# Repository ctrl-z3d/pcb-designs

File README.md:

# pcb-designs

A personal archive of PCB projects I've designed and built along the way. Schematics, board layouts, manufacturing files, and notes. This repo is mostly a learning log and reference for myself, but feel free to poke around if you found it useful.

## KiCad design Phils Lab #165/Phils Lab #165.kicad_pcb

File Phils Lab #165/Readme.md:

# Phil's Lab #165

KiCad project files for Phil's Lab video #165.

## Schematic

## PCB Layout

## 3D View (Top)

## 3D View (Bottom)

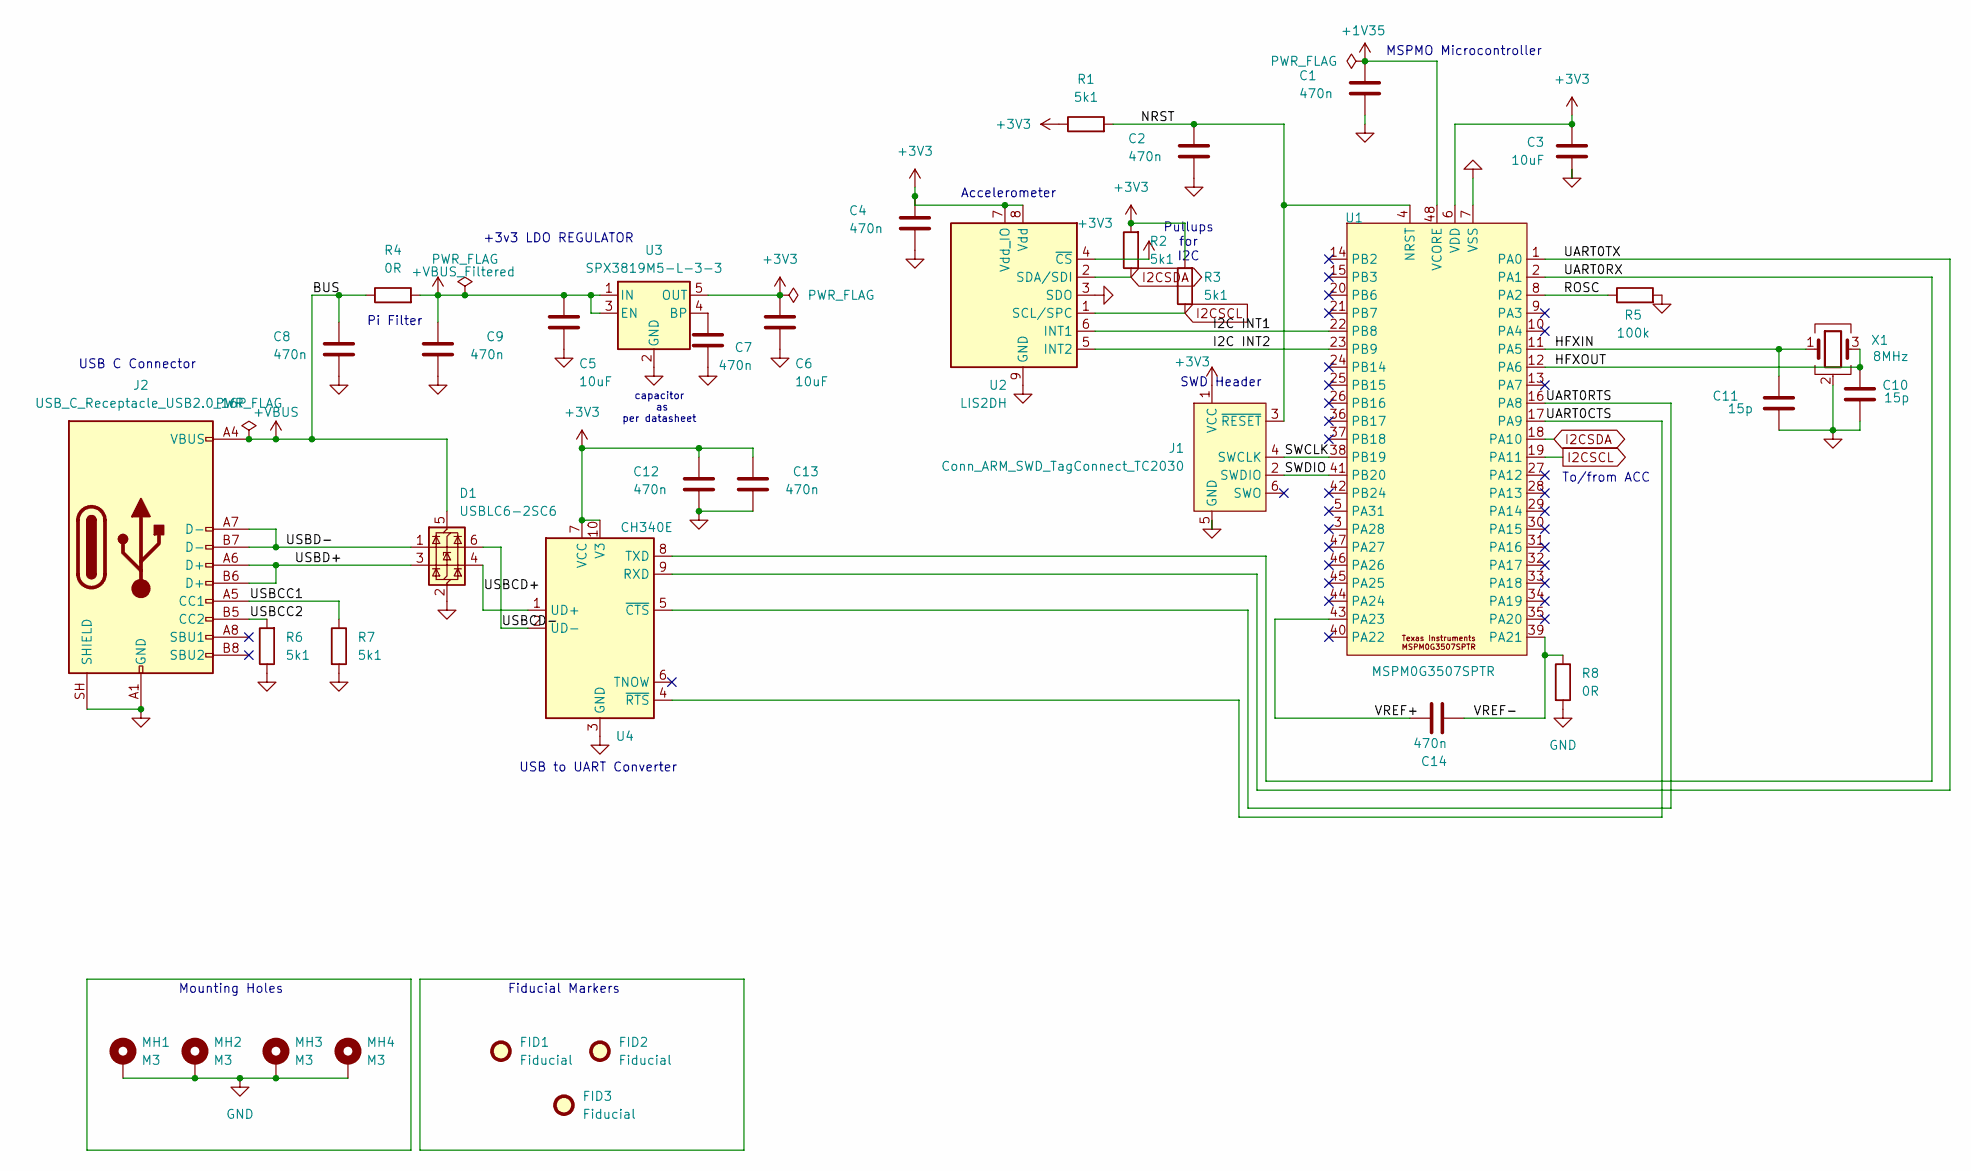
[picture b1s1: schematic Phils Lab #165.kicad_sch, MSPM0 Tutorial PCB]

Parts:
C1, C2, C4, C7, C8, C9, C12, C13, C14: 470n; C_0603_1608Metric
C3, C5, C6: 10uF; C_0805_2012Metric
C10, C11: 15p; C_0603_1608Metric
D1: USBLC6-2SC6; SOT-23-6
FID1, FID2, FID3: Fiducial; Fiducial_1mm_Mask2mm
J1: Conn_ARM_SWD_TagConnect_TC2030; Tag-Connect_TC2030-IDC-FP_2x03_P1.27mm_Vertical
J2: USB_C_Receptacle_USB2.0_16P; USB_C_Receptacle_GCT_USB4105-xx-A_16P_TopMnt_Horizontal
MH1, MH2, MH3, MH4: M3; MountingHole_3.2mm_M3_Pad_Via
R1, R2, R3, R6, R7: 5k1; R_0603_1608Metric_Pad0.98x0.95mm_HandSolder
R4, R8: 0R; R_0603_1608Metric_Pad0.98x0.95mm_HandSolder
R5: 100k; R_0603_1608Metric_Pad0.98x0.95mm_HandSolder
U1: MSPM0G3507SPTR; PT0048A-IPC_A
U2: LIS2DH; LGA-14_2x2mm_P0.35mm_LayoutBorder3x4y
U3: SPX3819M5-L-3-3; SOT-23-5
U4: CH340E; MSOP-10_3x3mm_P0.5mm
X1: 8MHz; Crystal_SMD_3225-4Pin_3.2x2.5mm

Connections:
+1V35: C1.1, U1.48 (VCORE)
+3V3: C3.1, C4.1, C6.1, C12.1, C13.1, J1.1 (VCC), R1.1, R2.2, R3.2, U1.6 (VDD), U2.4 (~CS), U2.7 (Vdd_IO), U2.8 (Vdd), U3.5 (OUT), U4.7 (VCC), U4.10 (V3)
+VBUS: C8.1, D1.5 (VBUS), J2.A4 (VBUS), J2.A9 (VBUS), J2.B4 (VBUS), J2.B9 (VBUS), R4.1
+VBUS_Filtered: C5.1, C9.1, R4.2, U3.1 (IN), U3.3 (EN)
/HFXIN: C11.1, U1.11 (PA5), X1.1
/HFXOUT: C10.1, U1.12 (PA6), X1.3
/I2C INT1: U1.22 (PB8), U2.6 (INT1)
/I2C INT2: U1.23 (PB9), U2.5 (INT2)
/NRST: C2.1, J1.3 (~RESET), R1.2, U1.4 (NRST)
/ROSC: R5.1, U1.8 (PA2)
/SWCLK: J1.4 (SWCLK), U1.38 (PB19)
/SWDIO: J1.2 (SWDIO), U1.41 (PB20)
/UART0CTS: U1.17 (PA9), U4.4 (~RTS)
/UART0RTS: U1.16 (PA8), U4.5 (~CTS)
/UART0RX: U1.2 (PA1), U4.8 (TXD)
/UART0TX: U1.1 (PA0), U4.9 (RXD)
/USBCC1: J2.A5 (CC1), R7.1
/USBCC2: J2.B5 (CC2), R6.2
/USBCD+: D1.4 (I/O2), U4.1 (UD+)
/USBCD-: D1.6 (I/O1), U4.2 (UD-)
/USBD+: D1.3 (I/O2), J2.A6 (D+), J2.B6 (D+)
/USBD-: D1.1 (I/O1), J2.A7 (D-), J2.B7 (D-)
/VREF+: C14.1, U1.43 (PA23)
/VREF-: C14.2, R8.1, U1.39 (PA21)
GND: C1.2, C2.2, C3.2, C4.2, C5.2, C6.2, C7.2, C8.2, C9.2, C10.2, C11.2, C12.2, C13.2, D1.2 (GND), J1.5 (GND), J2.A1 (GND), J2.A12 (GND), J2.B1 (GND), J2.B12 (GND), J2.SH (SHIELD), MH1.1 (1_1), MH2.1 (1_1), MH3.1 (1_1), MH4.1 (1_1), R5.2, R6.1, R7.2, R8.2, U1.7 (VSS), U2.3 (SDO), U2.9 (GND), U2.10 (GND), U2.11 (GND), U2.12 (GND), U2.13 (GND), U2.14 (GND), U3.2 (GND), U4.3 (GND), X1.2 (G), X1.4 (G)
I2CSCL: R3.1, U1.19 (PA11), U2.1 (SCL/SPC)
I2CSDA: R2.1, U1.18 (PA10), U2.2 (SDA/SDI)
unnamed: C7.1, U3.4 (BP)

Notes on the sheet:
MSPMO Microcontroller
Accelerometer
Mounting Holes
To/from ACC
USB C Connector
Fiducial Markers
Pi Filter
USB to UART Converter
capacitor as per datasheet
Pullups for I2C
+3v3 LDO REGULATOR
SWD Header

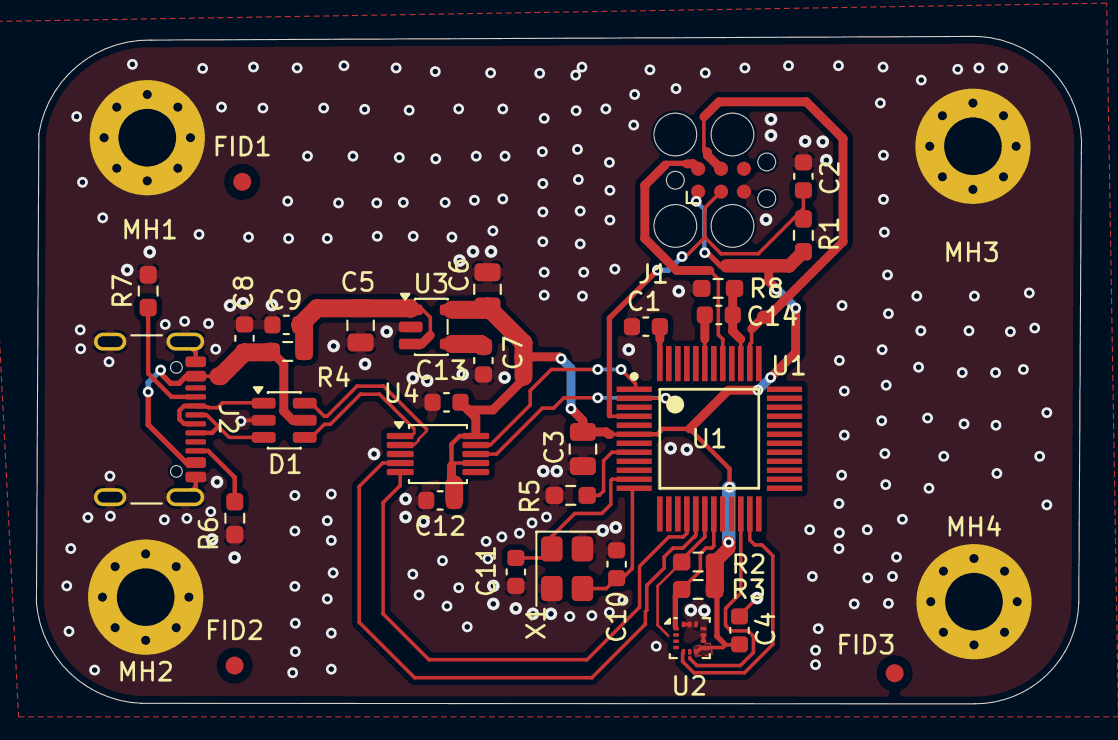
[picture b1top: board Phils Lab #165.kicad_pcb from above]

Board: 2 copper layers, 58.1 x 37.1 mm, 37 parts (0 on the bottom side), 28 nets.

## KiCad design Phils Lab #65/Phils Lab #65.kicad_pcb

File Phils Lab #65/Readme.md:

# Phil's Lab #65

KiCad project files for Phil's Lab video #65.

## Schematic

## PCB Layout

## 3D View

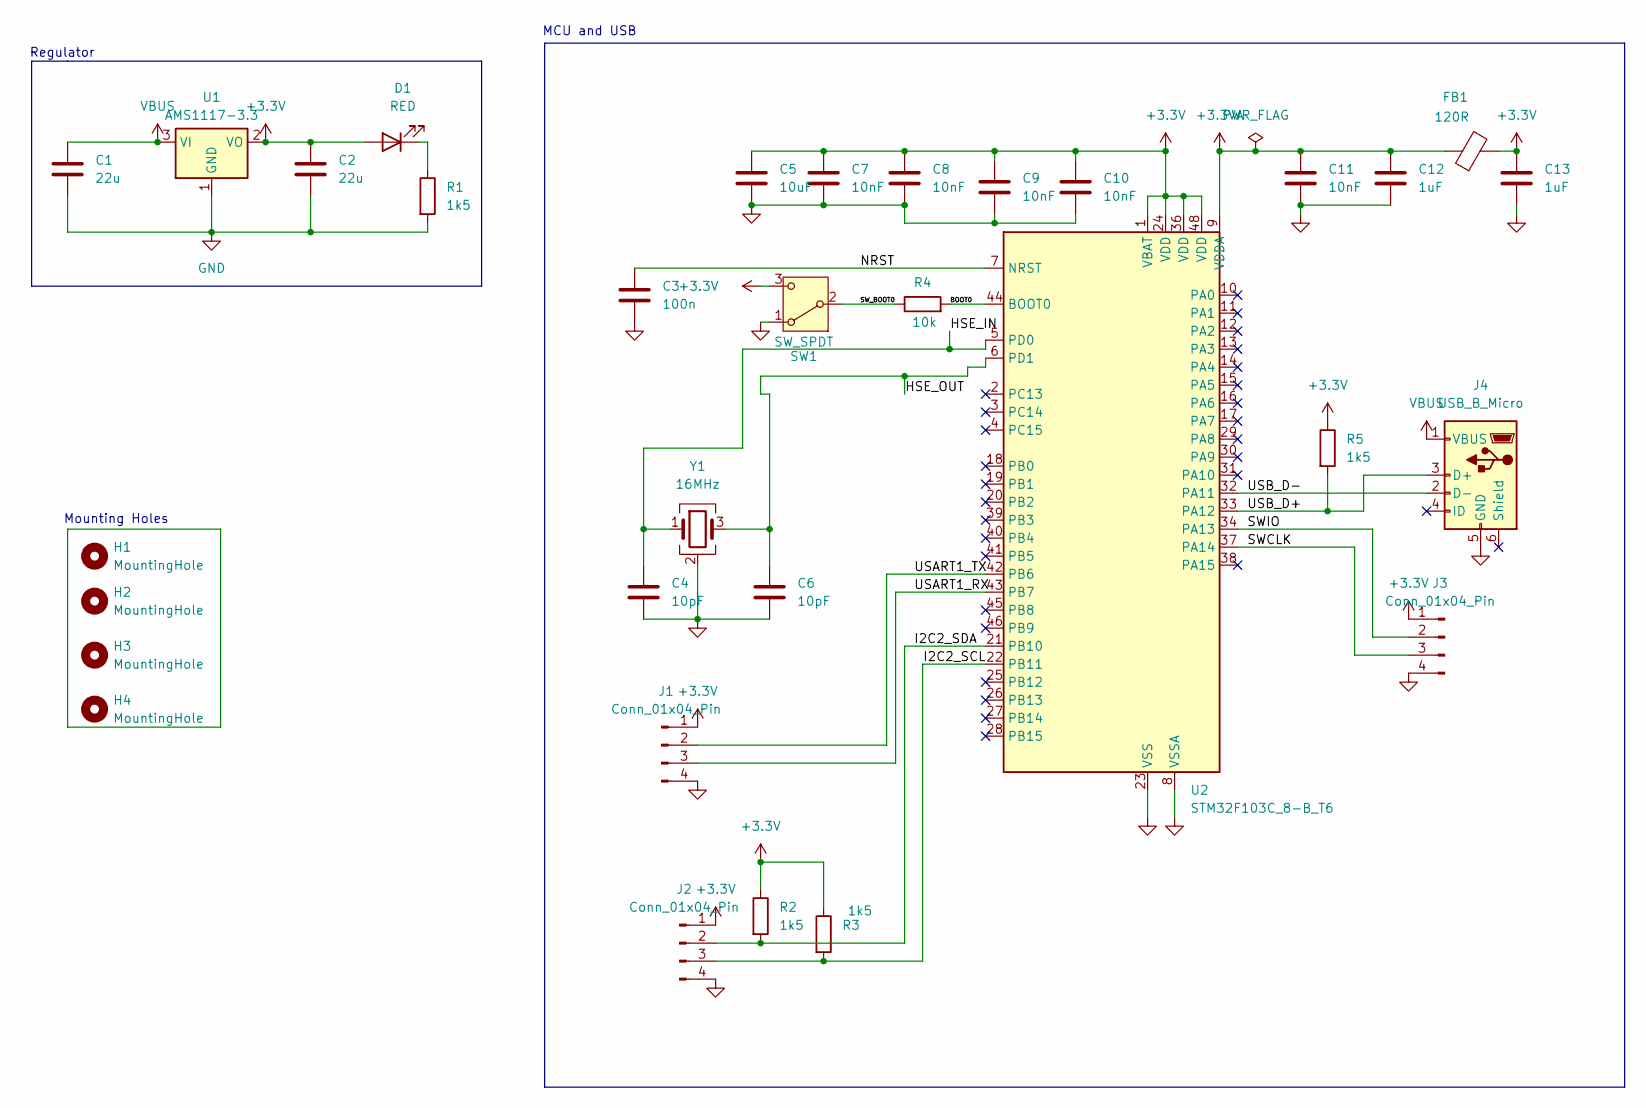
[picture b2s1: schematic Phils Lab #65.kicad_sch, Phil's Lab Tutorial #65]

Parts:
C1, C2: 22u; C_0805_2012Metric
C3: 100n; C_0402_1005Metric_Pad0.74x0.62mm_HandSolder
C4: 10pF; C_0402_1005Metric
C5: 10uF; C_0603_1608Metric_Pad1.08x0.95mm_HandSolder
C6: 10pF; C_0402_1005Metric_Pad0.74x0.62mm_HandSolder
C7, C8, C9, C10, C11: 10nF; C_0402_1005Metric
C12, C13: 1uF; C_0402_1005Metric
D1: RED; LED_0603_1608Metric
FB1: 120R; L_0603_1608Metric
H1, H2, H3, H4: MountingHole; MountingHole_2.2mm_M2
J1, J2, J3: Conn_01x04_Pin; Molex_KK-254_AE-6410-04A_1x04_P2.54mm_Vertical
J4: USB_B_Micro; USB_Micro-B_Wuerth_629105150521_CircularHoles
R1, R2, R3, R5: 1k5; R_0402_1005Metric_Pad0.72x0.64mm_HandSolder
R4: 10k; R_0402_1005Metric_Pad0.72x0.64mm_HandSolder
SW1: SW_SPDT; SW_SPDT_PCM12
U1: AMS1117-3.3; SOT-223-3_TabPin2
U2: STM32F103C_8-B_T6; LQFP-48_7x7mm_P0.5mm
Y1: 16MHz; Crystal_SMD_3225-4Pin_3.2x2.5mm

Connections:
+3.3V: C2.1, C5.1, C7.1, C8.1, C9.1, C10.1, C13.1, D1.2 (A), FB1.2, J1.1, J2.1, J3.1, R2.1, R3.1, R5.1, SW1.3 (C), U1.2 (VO), U2.1 (VBAT), U2.24 (VDD), U2.36 (VDD), U2.48 (VDD)
+3.3VA: C11.1, C12.1, FB1.1, U2.9 (VDDA)
/BOOT0: R4.2, U2.44 (BOOT0)
/HSE_IN: C4.1, U2.5 (PD0), Y1.1
/HSE_OUT: C6.1, U2.6 (PD1), Y1.3
/I2C2_SCL: J2.3, R3.2, U2.22 (PB11)
/I2C2_SDA: J2.2, R2.2, U2.21 (PB10)
/NRST: C3.1, U2.7 (NRST)
/SWCLK: J3.3, U2.37 (PA14)
/SWIO: J3.2, U2.34 (PA13)
/SW_BOOT0: R4.1, SW1.2 (B)
/USART1_RX: J1.3, U2.43 (PB7)
/USART1_TX: J1.2, U2.42 (PB6)
/USB_D+: J4.3 (D+), R5.2, U2.33 (PA12)
/USB_D-: J4.2 (D-), U2.32 (PA11)
GND: C1.2, C2.2, C3.2, C4.2, C5.2, C6.2, C7.2, C8.2, C9.2, C10.2, C11.2, C12.2, C13.2, J1.4, J2.4, J3.4, J4.5 (GND), R1.2, SW1.1 (A), U1.1 (GND), U2.8 (VSSA), U2.23 (VSS), Y1.2 (G), Y1.4 (G)
unnamed: D1.1 (K), R1.1
VBUS: C1.1, J4.1 (VBUS), U1.3 (VI)

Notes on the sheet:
MCU and USB
Regulator
Mounting Holes

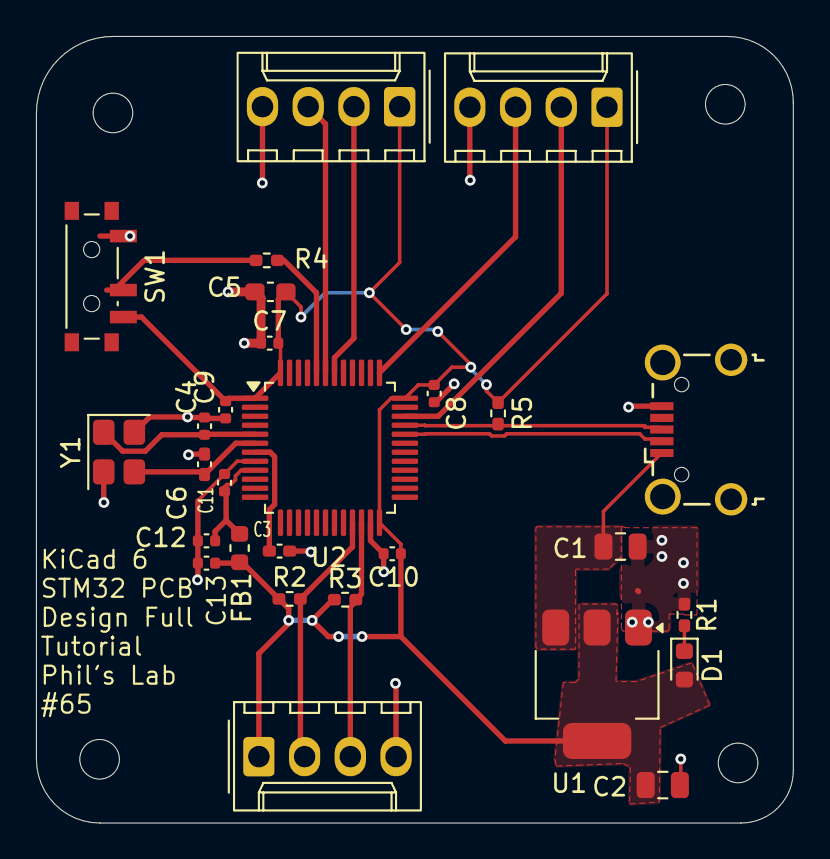
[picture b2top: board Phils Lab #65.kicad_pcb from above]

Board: 2 copper layers, 42.0 x 43.7 mm, 32 parts (0 on the bottom side), 18 nets.

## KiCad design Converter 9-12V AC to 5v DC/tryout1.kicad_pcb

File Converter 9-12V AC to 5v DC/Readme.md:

# 5V Linear Power Supply (AC-DC, L7805-based)

A small, DRC-clean KiCad PCB that converts low-voltage AC (from a transformer) into a regulated 5V DC output, using a full-wave bridge rectifier and an L7805 linear regulator.

## Overview

This board takes AC input from a Source, rectifies it, smooths it, and regulates it down to a clean 5V DC rail suitable for powering microcontrollers, sensors, relays, or other low-voltage electronics.

*Input:* 9–12V AC
*Output:* 5V DC, up to 1.5A
*Topology:* Bridge rectifier → smoothing capacitor → linear regulator → output filtering

AC IN → [Bridge Rectifier D1] → [C3 smoothing] → [L7805] → [C1/C2 decoupling] → DC OUT

## Schematic

| Ref | Part | Value / Part Number | Purpose |
|---|---|---|---|
| J1 | Screw terminal (2-pin) | General 2 pin | AC input |
| D1 | Bridge rectifier | KBP206 | Full-wave AC→DC rectification |
| C3 | Radial electrolytic | 1000µF | Bulk smoothing / ripple filtering |
| U1 | Linear regulator | L7805 (TO-220) | Regulates to 5V DC |
| C1 | Film/ceramic cap | 0.33µF | Regulator input decoupling (per datasheet) |
| C2 | Ceramic cap | 0.1µF | Regulator output decoupling (per datasheet) |
| J2 | Screw terminal (2-pin) | General 2 pin | Regulated 5V DC output |

Signal flow is a standard capacitor-input linear supply:

AC IN → [Bridge Rectifier D1] → [C3 smoothing] → [L7805] → [C1/C2 decoupling] → DC OUT

## Design notes

### KBP206 3D Model
*IMPORTANT NOTE: The KBP206 3D file is located within the footprints and schematics, kindly add it via KiCAD to view the 3D view of the Rectifier.*

### Why 9–12V AC input

The L7805 needs a minimum ~2V headroom above 5V to regulate correctly, even accounting for ripple sag between rectifier charging pulses. After accounting for bridge diode drops (~1.4V) and ripple, an AC input in the 9–12V RMS range lands the DC rail comfortably in the L7805's safe regulation window without excessive voltage headroom — excess headroom is wasted entirely as heat (see below), so this range was chosen deliberately rather than just "whatever transformer was on hand."

### Thermal design

Linear regulators dissipate power as heat according to:

P = (Vin − Vout) × Iout

At the top of the design envelope (12V AC → ~14V DC, 1.5A load), this comes out to roughly 13W dissipated in the TO-220 package — well beyond what the bare package can shed to ambient air. The board reserves a silkscreen-outlined footprint and mounting hole pattern (M3, 3.2mm clearance) for a bolt-on aluminum heatsink; a bare TO-220 or a small clip-on heatsink is *not sufficient* at this current level. See [Bill of Materials](#bill-of-materials) for the heatsink spec used.

### PCB layout

- *2-layer board.* All power routing (rectifier → smoothing cap → regulator → output) is on the bottom copper layer (B.Cu) at 1mm trace width, sized for the ripple/peak charging current through the bridge rectifier and smoothing cap, not just average load current.
- *Ground poured solid on both layers* (F.Cu and B.Cu), stitched together with vias, and set to *solid pad connection* (not thermal relief) rather than the KiCad default. This was a deliberate choice: thermal reliefs exist to make hand-soldering easier by limiting heat sinking into the pour, which is the opposite of what's wanted at the regulator's ground/tab connection, where good copper contact helps both current return and heat spreading.
- *Decoupling caps (C1, C2)* placed close to the regulator's IN/OUT pins to minimize trace inductance and keep them effective against fast transients, per the L7805 datasheet's recommended values.
- *Mounting holes* (M3, standard 3.2mm close-fit clearance) added at two points for mechanical stability, since the screw terminals will see repeated mechanical stress from wiring.

## Bill of Materials

| Qty | Part | Notes |
|---|---|---|
| 1 | KBP206 bridge rectifier | |
| 1 | L7805 (TO-220) | |
| 1 | 1000µF electrolytic capacitor | Radial, D12.5mm |
| 1 | 0.33µF capacitor | Per L7805 datasheet |
| 1 | 0.1µF capacitor | Per L7805 datasheet |
| 2 | 2-pin screw terminal block | 5.08mm pitch |
| 1 | TO-220 heatsink | Sized for ~9°C/W or better at full 1.5A load — see [Thermal design](#thermal-design) |
| 1 | M3 screw + hardware | Heatsink and/or board mounting |

## Status

- ✅ Schematic complete
- ✅ PCB layout routed
- ✅ DRC clean
- ⏳ Not yet fabricated / bench-tested

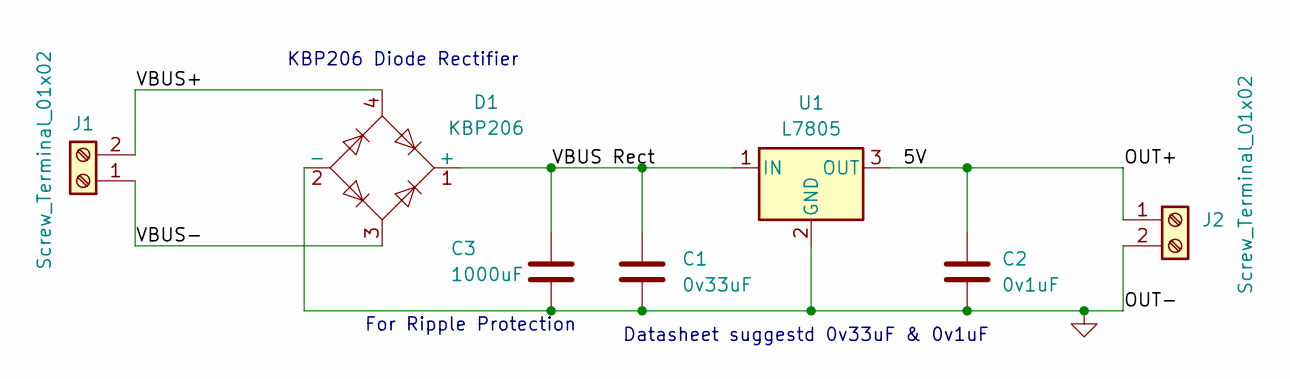
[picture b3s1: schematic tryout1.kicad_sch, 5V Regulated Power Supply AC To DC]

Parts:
C1: 0v33uF; C_Rect_L9.0mm_W3.2mm_P7.50mm_MKT
C2: 0v1uF; C_Radial_D6.3mm_H11.0mm_P2.50mm
C3: 1000uF; C_Radial_D12.5mm_H20.0mm_P5.00mm
D1: KBP206; Bridge_KBP206-4_P3.86mm
J1, J2: Screw_Terminal_01x02; TerminalBlock_Phoenix_MKDS-1,5-2-5.08_1x02_P5.08mm_Horizont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
U1: L7805; TO-220-3_Vertical

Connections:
/5V: C2.1, J2.1, U1.3 (OUT)
/VBUS Rect: C1.1, C3.1, D1.1 (+), U1.1 (IN)
/VBUS+: D1.4, J1.2
/VBUS-: D1.3, J1.1
GND: C1.2, C2.2, C3.2, D1.2 (-), J2.2, U1.2 (GND)

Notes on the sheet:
For Ripple Protection
KBP206 Diode Rectifier
Datasheet suggestd 0v33uF & 0v1uF

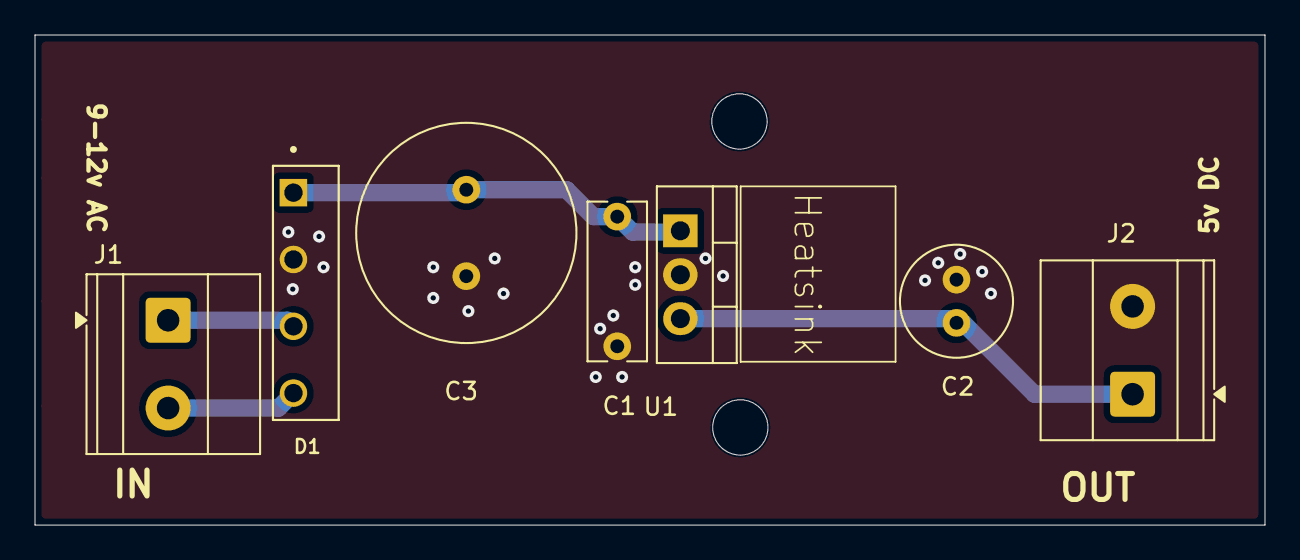
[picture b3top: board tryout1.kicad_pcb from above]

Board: 2 copper layers, 71.2 x 28.4 mm, 7 parts (0 on the bottom side), 5 nets.
